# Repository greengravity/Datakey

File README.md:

### Datastorage
## What is it?
In short, it is a physical offline-device to store secret information like account data or banking informations.  
While mobile apps can do things like this, its always possible to have some spyware installed with the last gaming app or whatever.  
Because of that i dont trust mobiles too much and so i decided to make this little project.  

# How it Works?
It is pretty simple, the device have 6 Buttons for input and a 1.7" Display for output.  
Just enter your pincode and you will be able to browse through your entries.  

Every entry have a name and up to 5 additional tokens to store informations like username/password or other things.  
You can add/delete or modify entries directly on the device, without the need of a mobile-device or computer.  

The tokens itself are entered with a virtual keyboard on the device.  
Its like entering the name with a gamecontroller on a gamingconsole.  

Everything entered will be encrypted with a masterkey and stored on a micro-sd card.  
The masterkey is a secret that only the user know, if it get lost, you may not be able to restore your data anymore.  

Usually the masterkey is stored in the device, so you dont need to rember it all the time.  
But if you or someone else mess up the pincode verification, the masterkey get deleted from the device (for security reasons).  
Thats why it is important to have the masterkey stored or memorized safely.  

The Device can also act as an keyboard.  
After you connected the device to your pc via usb, you can select an entry/token and push it to the pc.  
like entering the data with a keyboard.  
This type of communication is pretty much one-way, so the connected system cannot control the output of the device.  
It should be safe to use it like that.  

# Features
- 128-Bit AES-CBC encryption over all entries
* Offline input/output
* USB-Keyboard function to push data to connected systems
* USB-Charging
* Long standby because of low power consumption ( about 2 years - 8.5müAmp usage with 150mAh Battery )
* Usage of Fat32 filesystem, so you can backup your data on your PC, this is safe because the data is completely encrypted, but make sure the masterkey stay separated from the data (dont store the masterkey on the pc too)
+ TETRIS :)

# What do you need to start?
- The Device
* An micro sd-card, formated with a Fat32 filesystem.
+ A micro-usb cable to charge the device

Enter the sd-card to the slot on the side of the device and open it.  
You will be questioned about the masterkey.  
Enter one, the longer the better.  
Then you will be questioned about your pincode.  
This looks like a game, but it is actually just a disguise as an additional security layer.  
Enter one and Reenter it, you can use all 6 buttons for it.  
You should end up on an empty screen showing the entrylist.  
Gratulations, you can now add/modify entries in your list, using the context menus.  

# Build the Device
To build the device you need a bunch of things

The electrical components (see components.csv in the Docs)  
The Printboard (see datakeyboard/ for the kicad project or datakeyboard/gerber for the gerberfiles to send to your pcb-maker)  
The MPLAB X IDE from microchip as well as an programmer device like the PICKit to build and programm the pic24fj128gb204 microcontroller  
A 3D Printer to print the housing.  
A tiny piece of thin copper or iron and something to cut it, it become the inlay for the housing to trigger the pogopins when open or close the cap.  
A possibility to solder SMD-Parts

Checkout c0pperdragon and his amazing HotPlate project on github for this (also available on tindie)

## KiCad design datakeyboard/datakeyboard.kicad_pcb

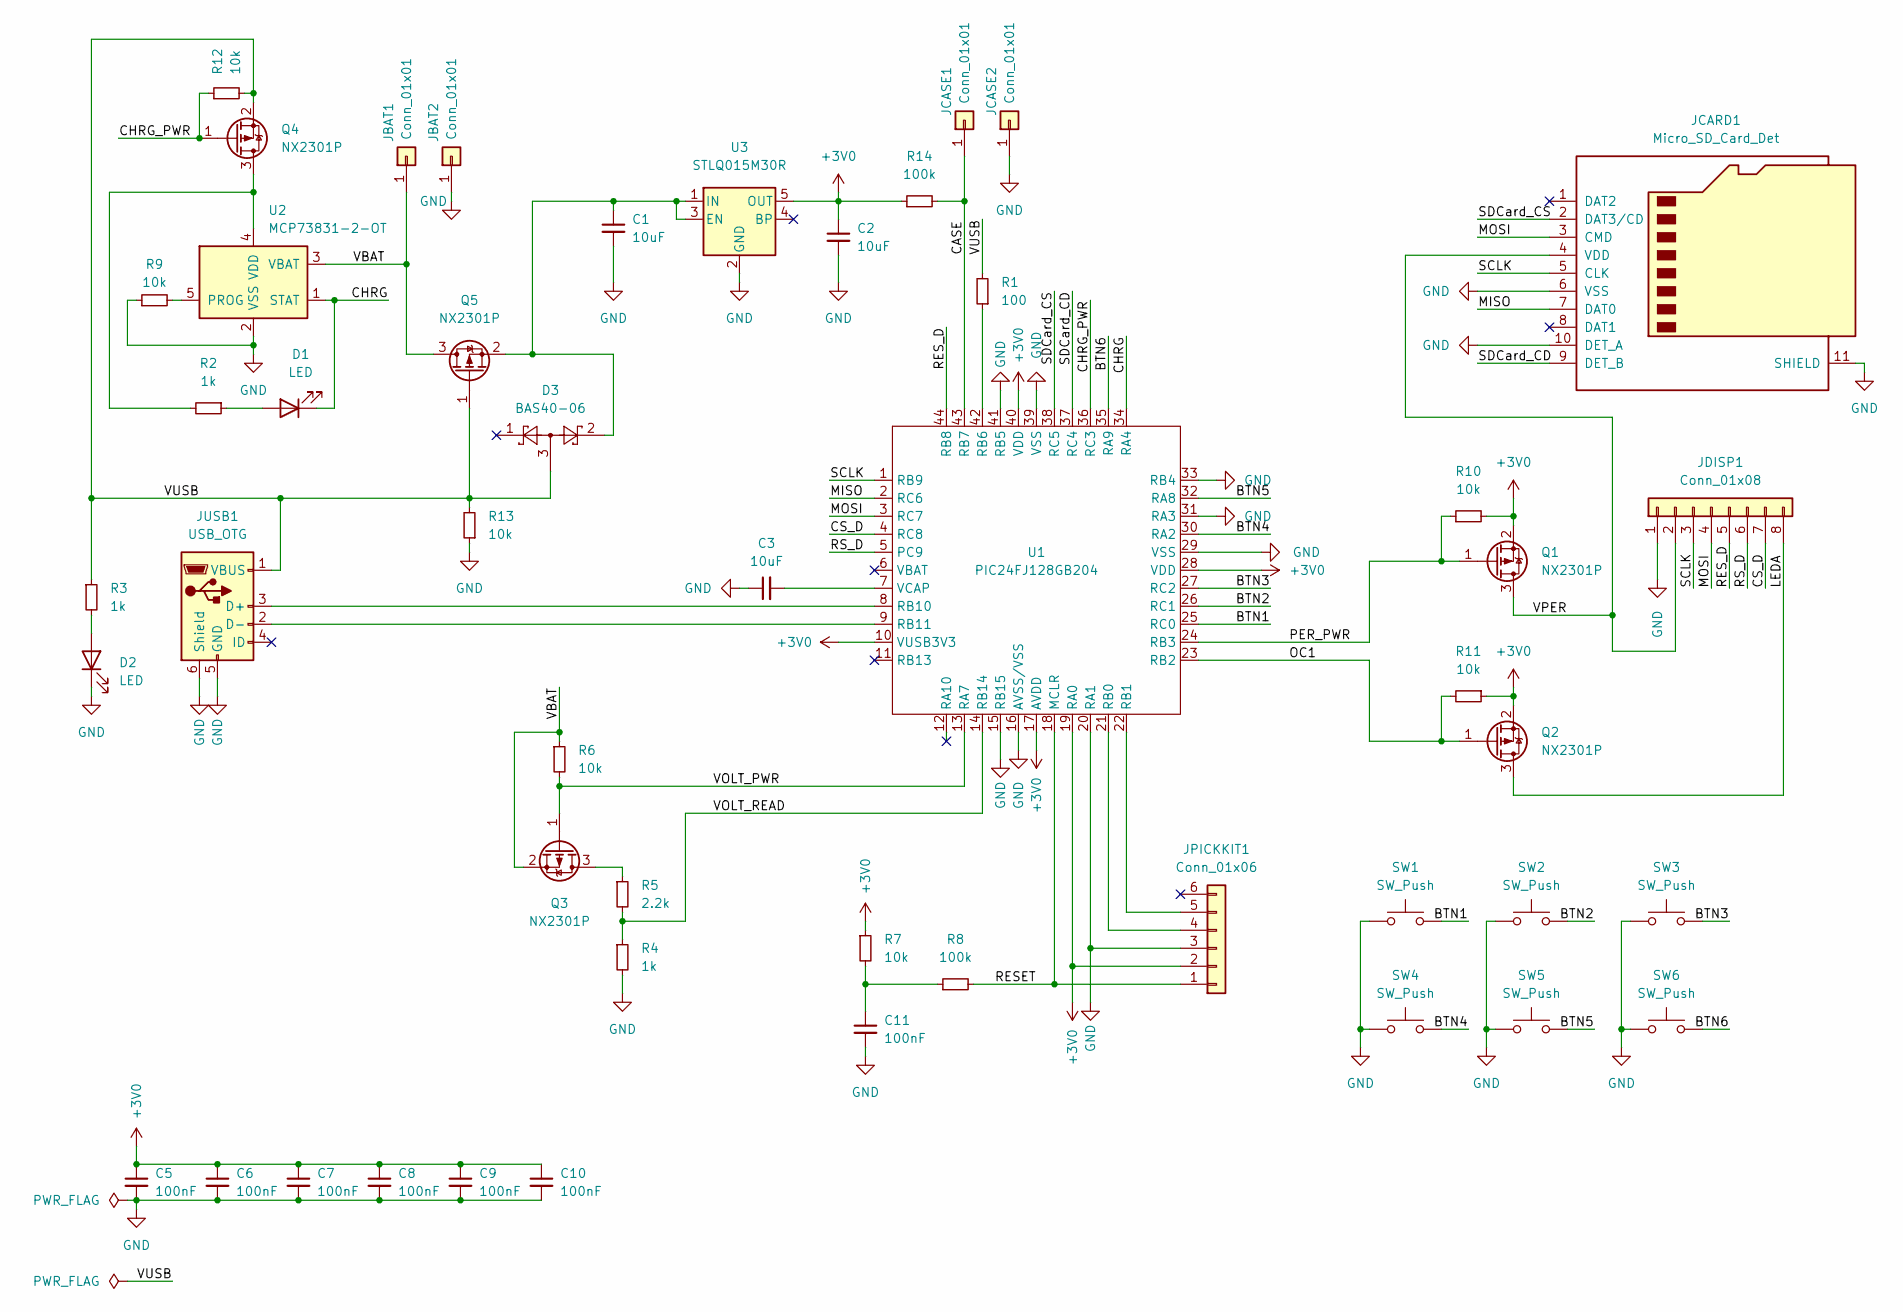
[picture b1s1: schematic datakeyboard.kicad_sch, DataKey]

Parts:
C1, C2, C3: 10uF; C_0805_2012Metric_Pad1.18x1.45mm_HandSolder
C5, C6, C7, C8, C9, C10, C11: 100nF; C_0603_1608Metric_Pad1.08x0.95mm_HandSolder
D1, D2: LED; D_1206_3216Metric_Pad1.42x1.75mm_HandSolder
D3: BAS40-06; SOT-23
JBAT1, JBAT2: Conn_01x01; TestPoint_Pad_2.0x2.0mm
JCARD1: Micro_SD_Card_Det; microSD_Unknown
JCASE1, JCASE2: Conn_01x01; TestPoint_Pad_2.0x2.0mm
JDISP1: Conn_01x08; PinHeader_1x08_P2.54mm_Vertical
JPICKKIT1: Conn_01x06; PinHeader_1x06_P2.54mm_Vertical
JUSB1: USB_OTG; USB_Micro-B_Unknown
Q1, Q2, Q3, Q4, Q5: NX2301P; SOT-23
R1: 100; R_0805_2012Metric_Pad1.20x1.40mm_HandSolder
R2, R3, R4: 1k; R_0805_2012Metric_Pad1.20x1.40mm_HandSolder
R5: 2.2k; R_0805_2012Metric_Pad1.20x1.40mm_HandSolder
R6, R7, R9, R10, R11, R12, R13: 10k; R_0805_2012Metric_Pad1.20x1.40mm_HandSolder
R8, R14: 100k; R_0805_2012Metric_Pad1.20x1.40mm_HandSolder
SW1, SW2, SW3, SW4, SW5, SW6: SW_Push; SW_Push_1P1T_NO_6x6mm_H9.5mm
U1: PIC24FJ128GB204; TQFP-44_10x10mm_P0.8mm
U2: MCP73831-2-OT; SOT-23-5
U3: STLQ015M30R; SOT-23-5

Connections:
+3V0: C2.1, C5.1, C6.1, C7.1, C8.1, C9.1, C10.1, JPICKKIT1.2, Q1.2 (S), Q2.2 (S), R7.1, R10.2, R11.1, R14.1, U1.10 (VUSB3V3), U1.17 (AVDD), U1.19 (RA0), U1.28 (VDD), U1.40 (VDD), U3.5 (OUT)
/BTN1: SW1.2, U1.25 (RC0)
/BTN2: SW2.2, U1.26 (RC1)
/BTN3: SW3.2, U1.27 (RC2)
/BTN4: SW4.2, U1.30 (RA2)
/BTN5: SW5.2, U1.32 (RA8)
/BTN6: SW6.2, U1.35 (RA9)
/CASE: JCASE1.1, R14.2, U1.43 (RB7)
/CHRG: D1.1 (K), U1.34 (RA4), U2.1 (STAT)
/CHRG_PWR: Q4.1 (G), R12.1, U1.36 (RC3)
/CS_D: JDISP1.7, U1.4 (RC8)
/LEDA: JDISP1.8, Q2.3 (D)
/MISO: JCARD1.7 (DAT0), U1.2 (RC6)
/MOSI: JCARD1.3 (CMD), JDISP1.4, U1.3 (RC7)
/OC1: Q2.1 (G), R11.2, U1.23 (RB2)
/PER_PWR: Q1.1 (G), R10.1, U1.24 (RB3)
/RESET: JPICKKIT1.1, R8.2, U1.18 (MCLR)
/RES_D: JDISP1.5, U1.44 (RB8)
/RS_D: JDISP1.6, U1.5 (PC9)
/SCLK: JCARD1.5 (CLK), JDISP1.3, U1.1 (RB9)
/SDCard_CD: JCARD1.9 (DET_B), U1.37 (RC4)
/SDCard_CS: JCARD1.2 (DAT3/CD), U1.38 (RC5)
/VBAT: JBAT1.1, Q3.2 (S), Q5.3 (D), R6.1, U2.3 (VBAT)
/VOLT_PWR: Q3.1 (G), R6.2, U1.13 (RA7)
/VOLT_READ: R4.1, R5.2, U1.14 (RB14)
/VPER: JCARD1.4 (VDD), JDISP1.2, Q1.3 (D)
/VUSB: D3.3, JUSB1.1 (VBUS), Q4.2 (S), Q5.1 (G), R1.2, R3.1, R12.2, R13.2
GND: C1.2, C2.2, C3.1, C5.2, C6.2, C7.2, C8.2, C9.2, C10.2, C11.2, D2.1 (K), JBAT2.1, JCARD1.6 (VSS), JCARD1.10 (DET_A), JCARD1.11 (SHIELD), JCASE2.1, JDISP1.1, JPICKKIT1.3, JUSB1.5 (GND), JUSB1.6 (Shield), R4.2, R9.1, R13.1, SW1.1, SW2.1, SW3.1, SW4.1, SW5.1, SW6.1, U1.15 (RB15), U1.16 (AVSS/VSS), U1.20 (RA1), U1.29 (VSS), U1.31 (RA3), U1.33 (RB4), U1.39 (VSS), U1.41 (RB5), U2.2 (VSS), U3.2 (GND)
unnamed: C1.1, D3.2, Q5.2 (S), U3.1 (IN), U3.3 (EN)
unnamed: C3.2, U1.7 (VCAP)
unnamed: C11.1, R7.2, R8.1
unnamed: D1.2 (A), R2.1
unnamed: D2.2 (A), R3.2
unnamed: JPICKKIT1.4, U1.21 (RB0)
unnamed: JPICKKIT1.5, U1.22 (RB1)
unnamed: JUSB1.2 (D-), U1.9 (RB11)
unnamed: JUSB1.3 (D+), U1.8 (RB10)
unnamed: Q3.3 (D), R5.1
unnamed: Q4.3 (D), R2.2, U2.4 (VDD)
unnamed: R1.1, U1.42 (RB6)
unnamed: R9.2, U2.5 (PROG)

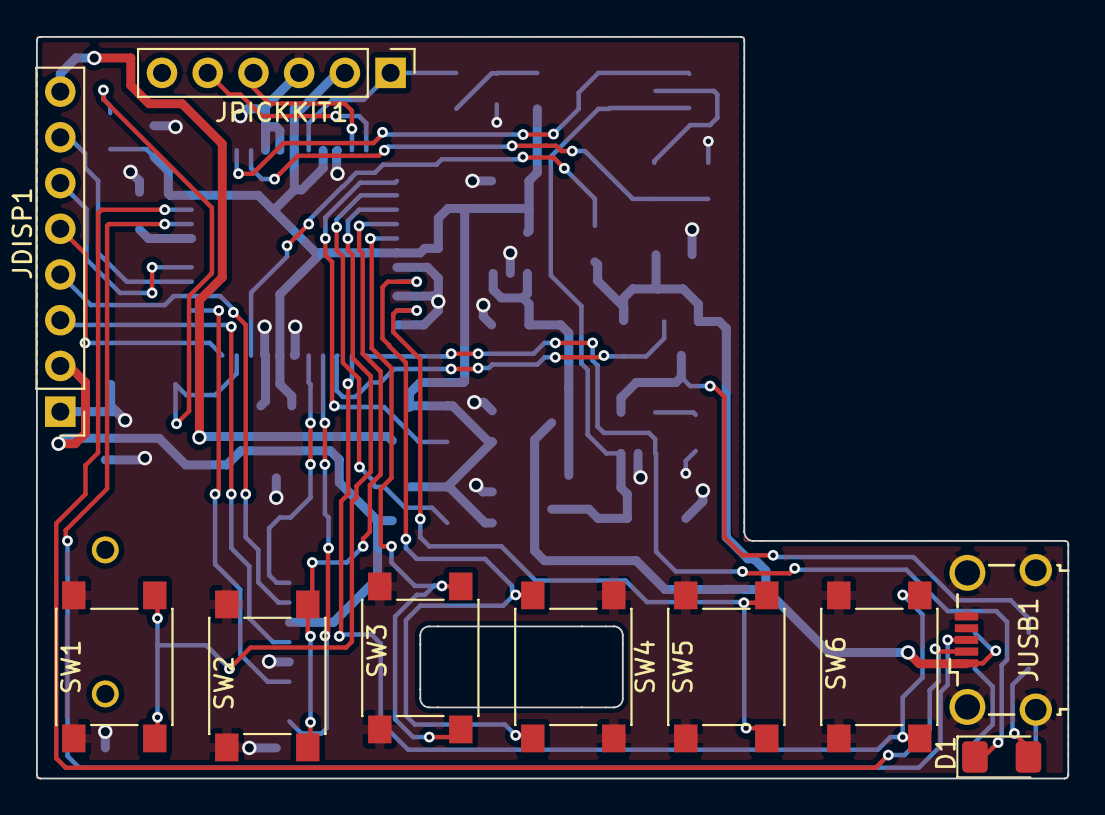
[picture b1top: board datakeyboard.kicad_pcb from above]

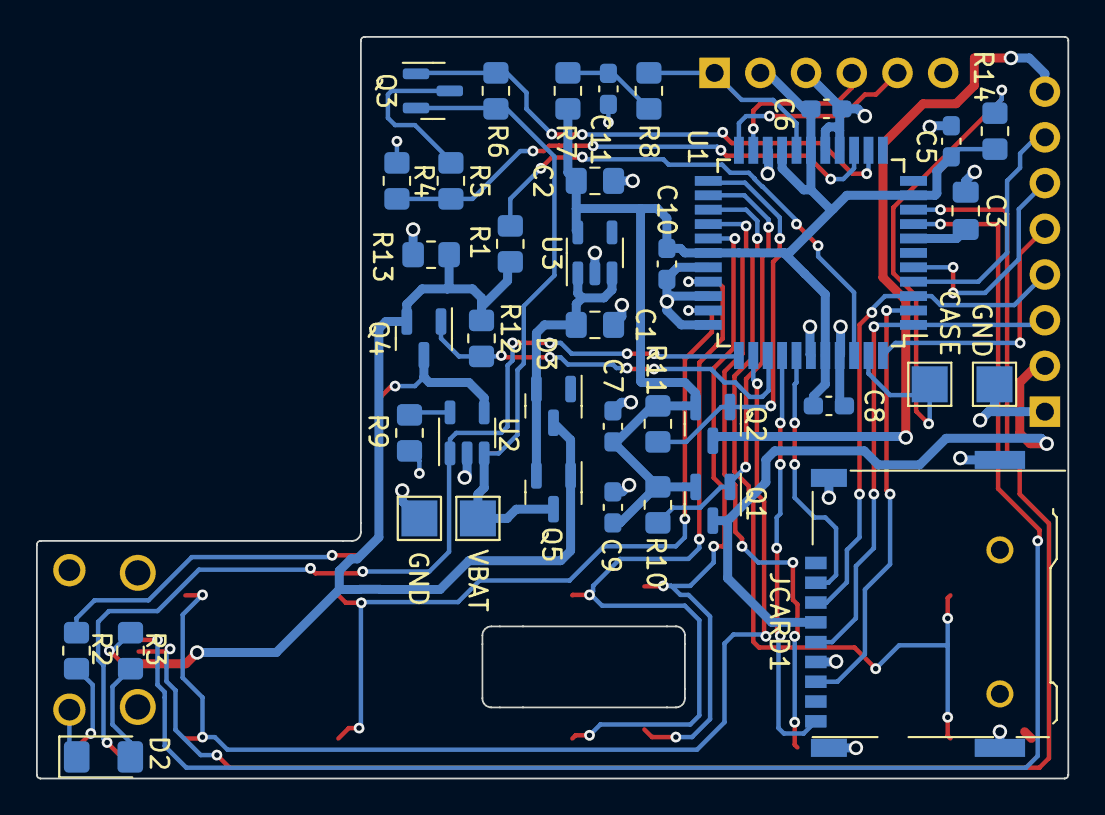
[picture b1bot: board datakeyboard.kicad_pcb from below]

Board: 2 copper layers, 57.3 x 41.2 mm, 49 parts (39 on the bottom side), 41 nets.

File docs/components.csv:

Item,Qty,Reference(s),Value,LibPart,Footprint,Datasheet
1,3,"C1, C2, C3",10uF,Device:C_Small,Capacitor_SMD:C_0805_2012Metric_Pad1.18x1.45mm_HandSolder,~
2,7,"C5, C6, C7, C8, C9, C10, C11",100nF,Device:C_Small,Capacitor_SMD:C_0603_1608Metric_Pad1.08x0.95mm_HandSolder,~
3,2,"D1, D2",LED,Device:LED,Diode_SMD:D_1206_3216Metric_Pad1.42x1.75mm_HandSolder,~
4,1,D3,BAS40-06,Library:BAS40-06,Package_TO_SOT_SMD:SOT-23,~
6,1,JCARD1,Micro_SD_Card_Det,Connector:Micro_SD_Card_Det,Library:microSD_Unknown,"Micro SD-Card slot, have a look at the image in the doc folder for the correct dimensions that match the footprint"
7,1,JDISP1,Conn_01x08,Connector_Generic:Conn_01x08,Connector_PinHeader_2.54mm:PinHeader_1x08_P2.54mm_Vertical,Display from A-Z Delivery – have a look at the datasheet in the doc folder
9,1,JUSB1,USB_OTG,Connector:USB_OTG,Library:USB_Micro-B_Unknown, ~
10,5,"Q1, Q2, Q3, Q4, Q5",NX2301P,Transistor_FET:BSS83P,Package_TO_SOT_SMD:SOT-23,~
11,1,R1,100,Device:R_Small,Resistor_SMD:R_0805_2012Metric_Pad1.20x1.40mm_HandSolder,~
12,3,"R2, R3, R4",1k,Device:R_Small,Resistor_SMD:R_0805_2012Metric_Pad1.20x1.40mm_HandSolder,~
13,1,R5,2.2k,Device:R_Small,Resistor_SMD:R_0805_2012Metric_Pad1.20x1.40mm_HandSolder,~
14,7,"R6, R7, R9, R10, R11, R12, R13",10k,Device:R_Small,Resistor_SMD:R_0805_2012Metric_Pad1.20x1.40mm_HandSolder,~
15,1,R8,100k,Device:R_Small,Resistor_SMD:R_0805_2012Metric_Pad1.20x1.40mm_HandSolder,~
16,6,"SW1, SW2, SW3, SW4, SW5, SW6",SW_Push,Switch:SW_Push,Button_Switch_SMD:SW_Push_1P1T_NO_6x6mm_H9.5mm,~
17,1,U1,PIC24FJ128GB204,Library:PIC24FJ128GB204,Package_QFP:TQFP-44_10x10mm_P0.8mm,
18,1,U2,MCP73831-2-OT,Battery_Management:MCP73831-2-OT,Package_TO_SOT_SMD:SOT-23-5,~
19,1,U3,STLQ015M30R,Regulator_Linear:AP131-30,Package_TO_SOT_SMD:SOT-23-5,~
20,2,,33mm extended,Pogopins,,~ soldered with fine cables to JCASE1 and JCASE2
21,1,,"3,7V, 150mAh ",Lipo-Battery,,https://www.amazon.de/dp/B08215WQMQ?ref=ppx_yo2ov_dt_b_produ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

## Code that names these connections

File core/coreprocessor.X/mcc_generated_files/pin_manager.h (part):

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#define IO_RA10_SetDigitalOutput() (_TRISA10 = 0)
/**
  @Summary
    Sets the GPIO pin, RA2, high using LATA2.

  @Description
    Sets the GPIO pin, RA2, high using LATA2.

  @Preconditions
    The RA2 must be set to an output.
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#define BTN4_SetHigh()          (_LATA2 = 1)
/**
  @Summary
    Sets the GPIO pin, RA2, low using LATA2.

  @Description
    Sets the GPIO pin, RA2, low using LATA2.

  @Preconditions
    The RA2 must be set to an output.
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#define BTN4_SetLow()           (_LATA2 = 0)
/**
  @Summary
    Toggles the GPIO pin, RA2, using LATA2.

  @Description
    Toggles the GPIO pin, RA2, using LATA2.

  @Preconditions
    The RA2 must be set to an output.
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#define BTN4_Toggle()           (_LATA2 ^= 1)
/**
  @Summary
    Reads the value of the GPIO pin, RA2.

  @Description
    Reads the value of the GPIO pin, RA2.

  @Preconditions
    None.
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    </code>

*/
#define BTN4_GetValue()         _RA2
/**
  @Summary
    Configures the GPIO pin, RA2, as an input.

  @Description
    Configures the GPIO pin, RA2, as an input.

  @Preconditions
    None.
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#define BTN4_SetDigitalInput()  (_TRISA2 = 1)
/**
  @Summary
    Configures the GPIO pin, RA2, as an output.

  @Description
    Configures the GPIO pin, RA2, as an output.

  @Preconditions
    None.
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#define BTN4_SetDigitalOutput() (_TRISA2 = 0)
/**
  @Summary
    Sets the GPIO pin, RA3, high using LATA3.

  @Description
    Sets the GPIO pin, RA3, high using LATA3.

  @Preconditions
    The RA3 must be set to an output.
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#define IO_RA3_SetHigh()          (_LATA3 = 1)
/**
  @Summary
    Sets the GPIO pin, RA3, low using LATA3.

  @Description
    Sets the GPIO pin, RA3, low using LATA3.

  @Preconditions
    The RA3 must be set to an output.
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#define IO_RA3_SetLow()           (_LATA3 = 0)
/**
  @Summary
    Toggles the GPIO pin, RA3, using LATA3.

  @Description
    Toggles the GPIO pin, RA3, using LATA3.

  @Preconditions
    The RA3 must be set to an output.
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#define IO_RA3_Toggle()           (_LATA3 ^= 1)
/**
  @Summary
    Reads the value of the GPIO pin, RA3.

  @Description
    Reads the value of the GPIO pin, RA3.

  @Preconditions
    None.
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    </code>

*/
#define IO_RA3_GetValue()         _RA3
/**
  @Summary
    Configures the GPIO pin, RA3, as an input.

  @Description
    Configures the GPIO pin, RA3, as an input.

  @Preconditions
    None.
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#define IO_RA3_SetDigitalInput()  (_TRISA3 = 1)
/**
  @Summary
    Configures the GPIO pin, RA3, as an output.

  @Description
    Configures the GPIO pin, RA3, as an output.

  @Preconditions
    None.
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#define IO_RA3_SetDigitalOutput() (_TRISA3 = 0)
/**
  @Summary
    Sets the GPIO pin, RA4, high using LATA4.

  @Description
    Sets the GPIO pin, RA4, high using LATA4.

  @Preconditions
    The RA4 must be set to an output.
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#define CHRG_SetHigh()          (_LATA4 = 1)
/**
  @Summary
    Sets the GPIO pin, RA4, low using LATA4.

  @Description
    Sets the GPIO pin, RA4, low using LATA4.

  @Preconditions
    The RA4 must be set to an output.
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#define CHRG_SetLow()           (_LATA4 = 0)
/**
  @Summary
    Toggles the GPIO pin, RA4, using LATA4.

  @Description
    Toggles the GPIO pin, RA4, using LATA4.

  @Preconditions
    The RA4 must be set to an output.
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#define CHRG_Toggle()           (_LATA4 ^= 1)
/**
  @Summary
    Reads the value of the GPIO pin, RA4.

  @Description
    Reads the value of the GPIO pin, RA4.

  @Preconditions
    None.
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    </code>

*/
#define CHRG_GetValue()         _RA4
/**
  @Summary
    Configures the GPIO pin, RA4, as an input.

  @Description
    Configures the GPIO pin, RA4, as an input.

  @Preconditions
    None.
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#define CHRG_SetDigitalInput()  (_TRISA4 = 1)
/**
  @Summary
    Configures the GPIO pin, RA4, as an output.

  @Description
    Configures the GPIO pin, RA4, as an output.

  @Preconditions
    None.
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#define CHRG_SetDigitalOutput() (_TRISA4 = 0)
/**
  @Summary
    Sets the GPIO pin, RA7, high using LATA7.

  @Description
    Sets the GPIO pin, RA7, high using LATA7.

  @Preconditions
    The RA7 must be set to an output.
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#define VOLT_PWR_SetHigh()          (_LATA7 = 1)
/**
  @Summary
    Sets the GPIO pin, RA7, low using LATA7.

  @Description
    Sets the GPIO pin, RA7, low using LATA7.

  @Preconditions
    The RA7 must be set to an output.
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#define VOLT_PWR_SetLow()           (_LATA7 = 0)
/**
  @Summary
    Toggles the GPIO pin, RA7, using LATA7.

  @Description
    Toggles the GPIO pin, RA7, using LATA7.

  @Preconditions
    The RA7 must be set to an output.
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#define VOLT_PWR_Toggle()           (_LATA7 ^= 1)
/**
  @Summary
    Reads the value of the GPIO pin, RA7.

  @Description
    Reads the value of the GPIO pin, RA7.

  @Preconditions
    None.
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    </code>

*/
#define VOLT_PWR_GetValue()         _RA7
/**
  @Summary
    Configures the GPIO pin, RA7, as an input.

  @Description
    Configures the GPIO pin, RA7, as an input.

  @Preconditions
    None.
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#define VOLT_PWR_SetDigitalInput()  (_TRISA7 = 1)
/**
  @Summary
    Configures the GPIO pin, RA7, as an output.

  @Description
    Configures the GPIO pin, RA7, as an output.

  @Preconditions
    None.
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#define VOLT_PWR_SetDigitalOutput() (_TRISA7 = 0)
/**
  @Summary
    Sets the GPIO pin, RA8, high using LATA8.

  @Description
    Sets the GPIO pin, RA8, high using LATA8.

  @Preconditions
    The RA8 must be set to an output.
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#define BTN5_SetHigh()          (_LATA8 = 1)
/**
  @Summary
    Sets the GPIO pin, RA8, low using LATA8.

  @Description
    Sets the GPIO pin, RA8, low using LATA8.

  @Preconditions
    The RA8 must be set to an output.
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#define BTN5_SetLow()           (_LATA8 = 0)
/**
  @Summary
    Toggles the GPIO pin, RA8, using LATA8.

  @Description
    Toggles the GPIO pin, RA8, using LATA8.

  @Preconditions
    The RA8 must be set to an output.
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#define BTN5_Toggle()           (_LATA8 ^= 1)
/**
  @Summary
    Reads the value of the GPIO pin, RA8.

  @Description
    Reads the value of the GPIO pin, RA8.

  @Preconditions
    None.
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    </code>

*/
#define BTN5_GetValue()         _RA8
/**
  @Summary
    Configures the GPIO pin, RA8, as an input.

  @Description
    Configures the GPIO pin, RA8, as an input.

  @Preconditions
    None.
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#define BTN5_SetDigitalInput()  (_TRISA8 = 1)
/**
  @Summary
    Configures the GPIO pin, RA8, as an output.

  @Description
    Configures the GPIO pin, RA8, as an output.

  @Preconditions
    None.
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#define BTN5_SetDigitalOutput() (_TRISA8 = 0)
/**
  @Summary
    Sets the GPIO pin, RA9, high using LATA9.

  @Description
    Sets the GPIO pin, RA9, high using LATA9.

  @Preconditions
    The RA9 must be set to an output.
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#define BTN6_SetHigh()          (_LATA9 = 1)
/**
  @Summary
    Sets the GPIO pin, RA9, low using LATA9.

  @Description
    Sets the GPIO pin, RA9, low using LATA9.

  @Preconditions
    The RA9 must be set to an output.
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#define BTN6_SetLow()           (_LATA9 = 0)
/**
  @Summary
    Toggles the GPIO pin, RA9, using LATA9.

  @Description
    Toggles the GPIO pin, RA9, using LATA9.

  @Preconditions
    The RA9 must be set to an output.
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#define BTN6_Toggle()           (_LATA9 ^= 1)
/**
  @Summary
    Reads the value of the GPIO pin, RA9.

  @Description
    Reads the value of the GPIO pin, RA9.

  @Preconditions
    None.
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    </code>

*/
#define BTN6_GetValue()         _RA9
/**
  @Summary
    Configures the GPIO pin, RA9, as an input.

  @Description
    Configures the GPIO pin, RA9, as an input.

  @Preconditions
    None.
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#define BTN6_SetDigitalInput()  (_TRISA9 = 1)
/**
  @Summary
    Configures the GPIO pin, RA9, as an output.

  @Description
    Configures the GPIO pin, RA9, as an output.

  @Preconditions
    None.
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#define BTN6_SetDigitalOutput() (_TRISA9 = 0)
/**
  @Summary
    Sets the GPIO pin, RB10, high using LATB10.

  @Description
    Sets the GPIO pin, RB10, high using LATB10.

  @Preconditions
    The RB10 must be set to an output.
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#define D_PLUS_SetHigh()          (_LATB10 = 1)
/**
  @Summary
    Sets the GPIO pin, RB10, low using LATB10.

  @Description
    Sets the GPIO pin, RB10, low using LATB10.

  @Preconditions
    The RB10 must be set to an output.
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#define D_PLUS_SetLow()           (_LATB10 = 0)
/**
  @Summary
    Toggles the GPIO pin, RB10, using LATB10.

  @Description
    Toggles the GPIO pin, RB10, using LATB10.

  @Preconditions
    The RB10 must be set to an output.
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#define D_PLUS_Toggle()           (_LATB10 ^= 1)
/**
  @Summary
    Reads the value of the GPIO pin, RB10.

  @Description
    Reads the value of the GPIO pin, RB10.

  @Preconditions
    None.
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    </code>

*/
#define D_PLUS_GetValue()         _RB10
/**
  @Summary
    Configures the GPIO pin, RB10, as an input.

  @Description
    Configures the GPIO pin, RB10, as an input.

  @Preconditions
    None.
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#define D_PLUS_SetDigitalInput()  (_TRISB10 = 1)
/**
  @Summary
    Configures the GPIO pin, RB10, as an output.

  @Description
    Configures the GPIO pin, RB10, as an output.

  @Preconditions
    None.
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#define D_PLUS_SetDigitalOutput() (_TRISB10 = 0)
/**
  @Summary
    Sets the GPIO pin, RB11, high using LATB11.
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
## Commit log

2022-12-15 First core commit
2022-12-17 USB Basic Implementation
2022-12-21 Schematic symbol
2022-12-27 display base added
2022-12-27 docs
2022-12-28 More schematic
2022-12-29 Charging and battery protection
2023-01-02 Power supply
2023-01-03 Display light
2023-01-05 Wire up SDCard and buttons
2023-01-14 Continue schematics
2023-01-14 ADC-Converter
2023-01-16 assetgenerator
2023-01-19 Sleep enabled
2023-01-21 Adjust schematics to code
2023-01-21 Pin reconfiguration
2023-01-21 Fine tune schematic (grounding pins)
2023-01-25 Add case switch
2023-01-26 Pin input
2023-01-27 Board layout
2023-01-27 filesystem
2023-01-29 Start board layout
2023-01-29 Keyboard design
2023-01-29 Finish PCB layout
2023-01-29 Keyboard implementation
2023-01-30 Gerber files
2023-02-06 Basefunctions working
2023-02-16 Add second regulator to bypass charger
2023-02-16 Update PDF
2023-02-18 Control charging by microcontroller
2023-02-18 USB Progress
2023-02-19 Resize solder pads
2023-02-21 Last features
2023-02-26 Tetris added
2023-02-26 Redesign power supply to bypass charger when running from USB
2023-02-26 Add thermal reliefs on ground plane
2023-03-11 Reworked bootsequence
2023-03-18 Fix display orientation Switch VBAT, GND text on silk screen Movie VIAs out of the way of the button solder pads.
2023-03-19 Different Buttondefinitions
2023-11-05 Button configuration changed
2023-11-11 Added 3D Model for housing
2023-11-17 Reduce current to increase battery life
2023-11-19 Refine Charge control
2023-11-24 Fix the Masterkey verification after entering the Pin
2023-11-25 clean up stuff
2023-11-25 clean up
2023-12-22 Localization simplified
2023-12-25 Rescuetool updated
2023-12-30 added search function
2023-12-31 Bugfixes
2024-01-01 made masterkey input more intuitive

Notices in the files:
core/coreprocessor.X/mcc_generated_files/pin_manager.h:
(c) 2020 Microchip Technology Inc. and its subsidiaries. You may use this
